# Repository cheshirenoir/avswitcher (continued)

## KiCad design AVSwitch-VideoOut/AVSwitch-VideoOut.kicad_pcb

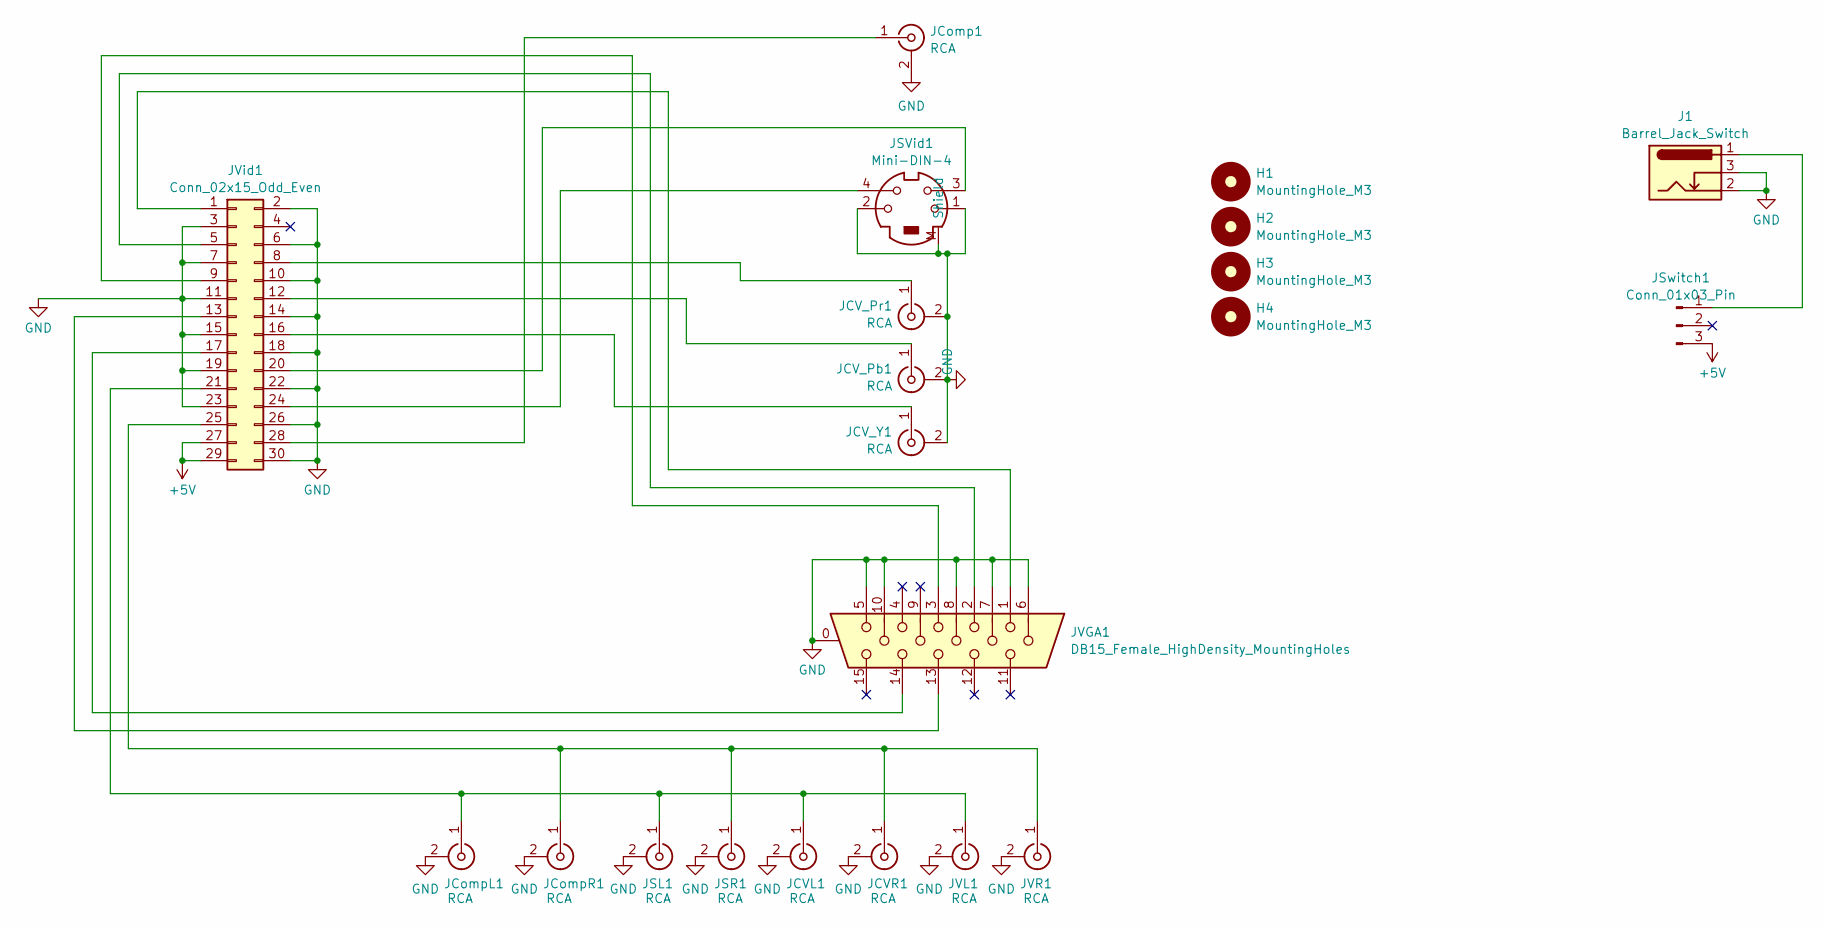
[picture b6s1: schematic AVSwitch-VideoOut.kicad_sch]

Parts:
H1, H2, H3, H4: MountingHole_M3; MountingHole_3.2mm_M3_DIN965_Pad
J1: Barrel_Jack_Switch; 2.1mm Socket (Vertical)
JCVL1: RCA; Vertical RCA (Altronics)
JCVR1: RCA; Vertical RCA (Altronics)
JCV_Pb1: RCA; Vertical RCA (Altronics)
JCV_Pr1: RCA; Vertical RCA (Altronics)
JCV_Y1: RCA; Vertical RCA (Altronics)
JComp1: RCA; Vertical RCA (Altronics)
JCompL1: RCA; Vertical RCA (Altronics)
JCompR1: RCA; Vertical RCA (Altronics)
JSL1: RCA; Vertical RCA (Altronics)
JSR1: RCA; Vertical RCA (Altronics)
JSVid1: Mini-DIN-4; Mini DIN 4 (Vertical)
JSwitch1: Conn_01x03_Pin; Ouplin 2.54mm
JVGA1: DB15_Female_HighDensity_MountingHoles; DSUB-15-HD_Female_Vertical_P2.29x1.98mm_MountingHoles
JVL1: RCA; Vertical RCA (Altronics)
JVR1: RCA; Vertical RCA (Altronics)
JVid1: Conn_02x15_Odd_Even; PinHeader_2x15_P2.54mm_Horizontal_Reverse

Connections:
+5V: JSwitch1.3, JVid1.27, JVid1.29
GND: J1.2, J1.3, JCVL1.2 (Ext), JCVR1.2 (Ext), JCV_Pb1.2 (Ext), JCV_Pr1.2 (Ext), JCV_Y1.2 (Ext), JComp1.2 (Ext), JCompL1.2 (Ext), JCompR1.2 (Ext), JSL1.2 (Ext), JSR1.2 (Ext), JSVid1.1, JSVid1.2, JSVid1.M (Shield), JVGA1.0, JVGA1.5, JVGA1.6, JVGA1.7, JVGA1.8, JVGA1.10, JVL1.2 (Ext), JVR1.2 (Ext), JVid1.2, JVid1.3, JVid1.6, JVid1.7, JVid1.10, JVid1.11, JVid1.14, JVid1.15, JVid1.18, JVid1.19, JVid1.22, JVid1.23, JVid1.26, JVid1.30
unnamed: JCVL1.1 (In), JCompL1.1 (In), JSL1.1 (In), JVL1.1 (In), JVid1.21
unnamed: JCVR1.1 (In), JCompR1.1 (In), JSR1.1 (In), JVR1.1 (In), JVid1.25
unnamed: JCV_Pb1.1 (In), JVid1.12
unnamed: JCV_Pr1.1 (In), JVid1.8
unnamed: JCV_Y1.1 (In), JVid1.16
unnamed: JComp1.1 (In), JVid1.28
unnamed: J1.1, JSwitch1.1
unnamed: JVGA1.1, JVid1.1
unnamed: JVGA1.2, JVid1.5
unnamed: JVGA1.3, JVid1.9
unnamed: JVGA1.13, JVid1.13
unnamed: JVGA1.14, JVid1.17
unnamed: JSVid1.3, JVid1.20
unnamed: JSVid1.4, JVid1.24

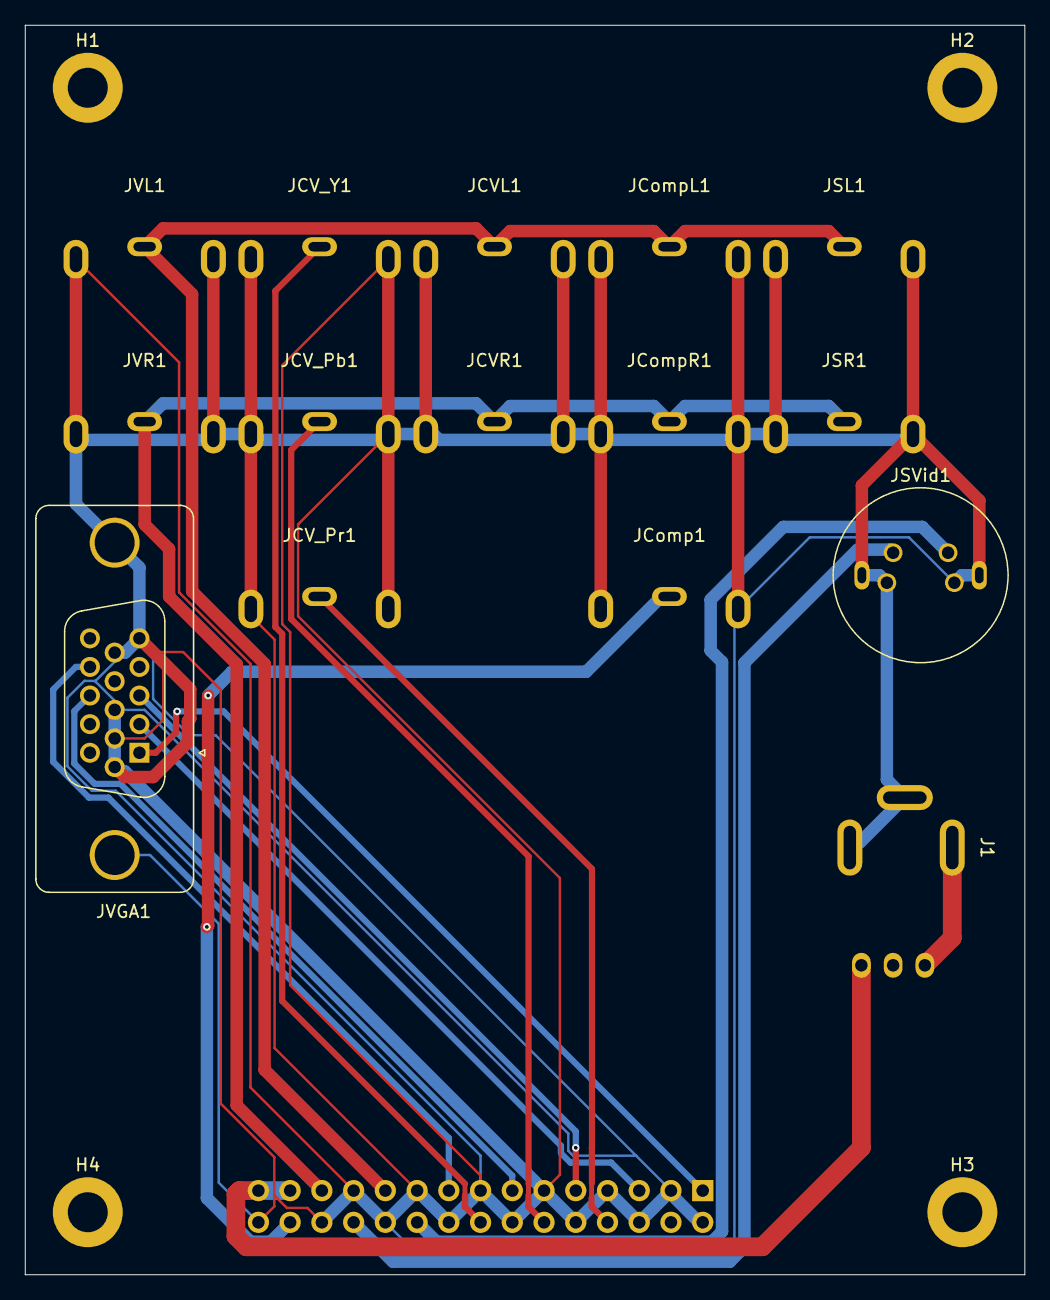
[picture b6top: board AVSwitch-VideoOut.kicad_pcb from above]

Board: 2 copper layers, 80.0 x 100.0 mm, 21 parts (1 on the bottom side), 16 nets.

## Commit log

2025-01-27 Add files via upload
    Let's put the correct image in.
2025-01-27 Add files via upload
    New version with better footprint and ground isolation.
